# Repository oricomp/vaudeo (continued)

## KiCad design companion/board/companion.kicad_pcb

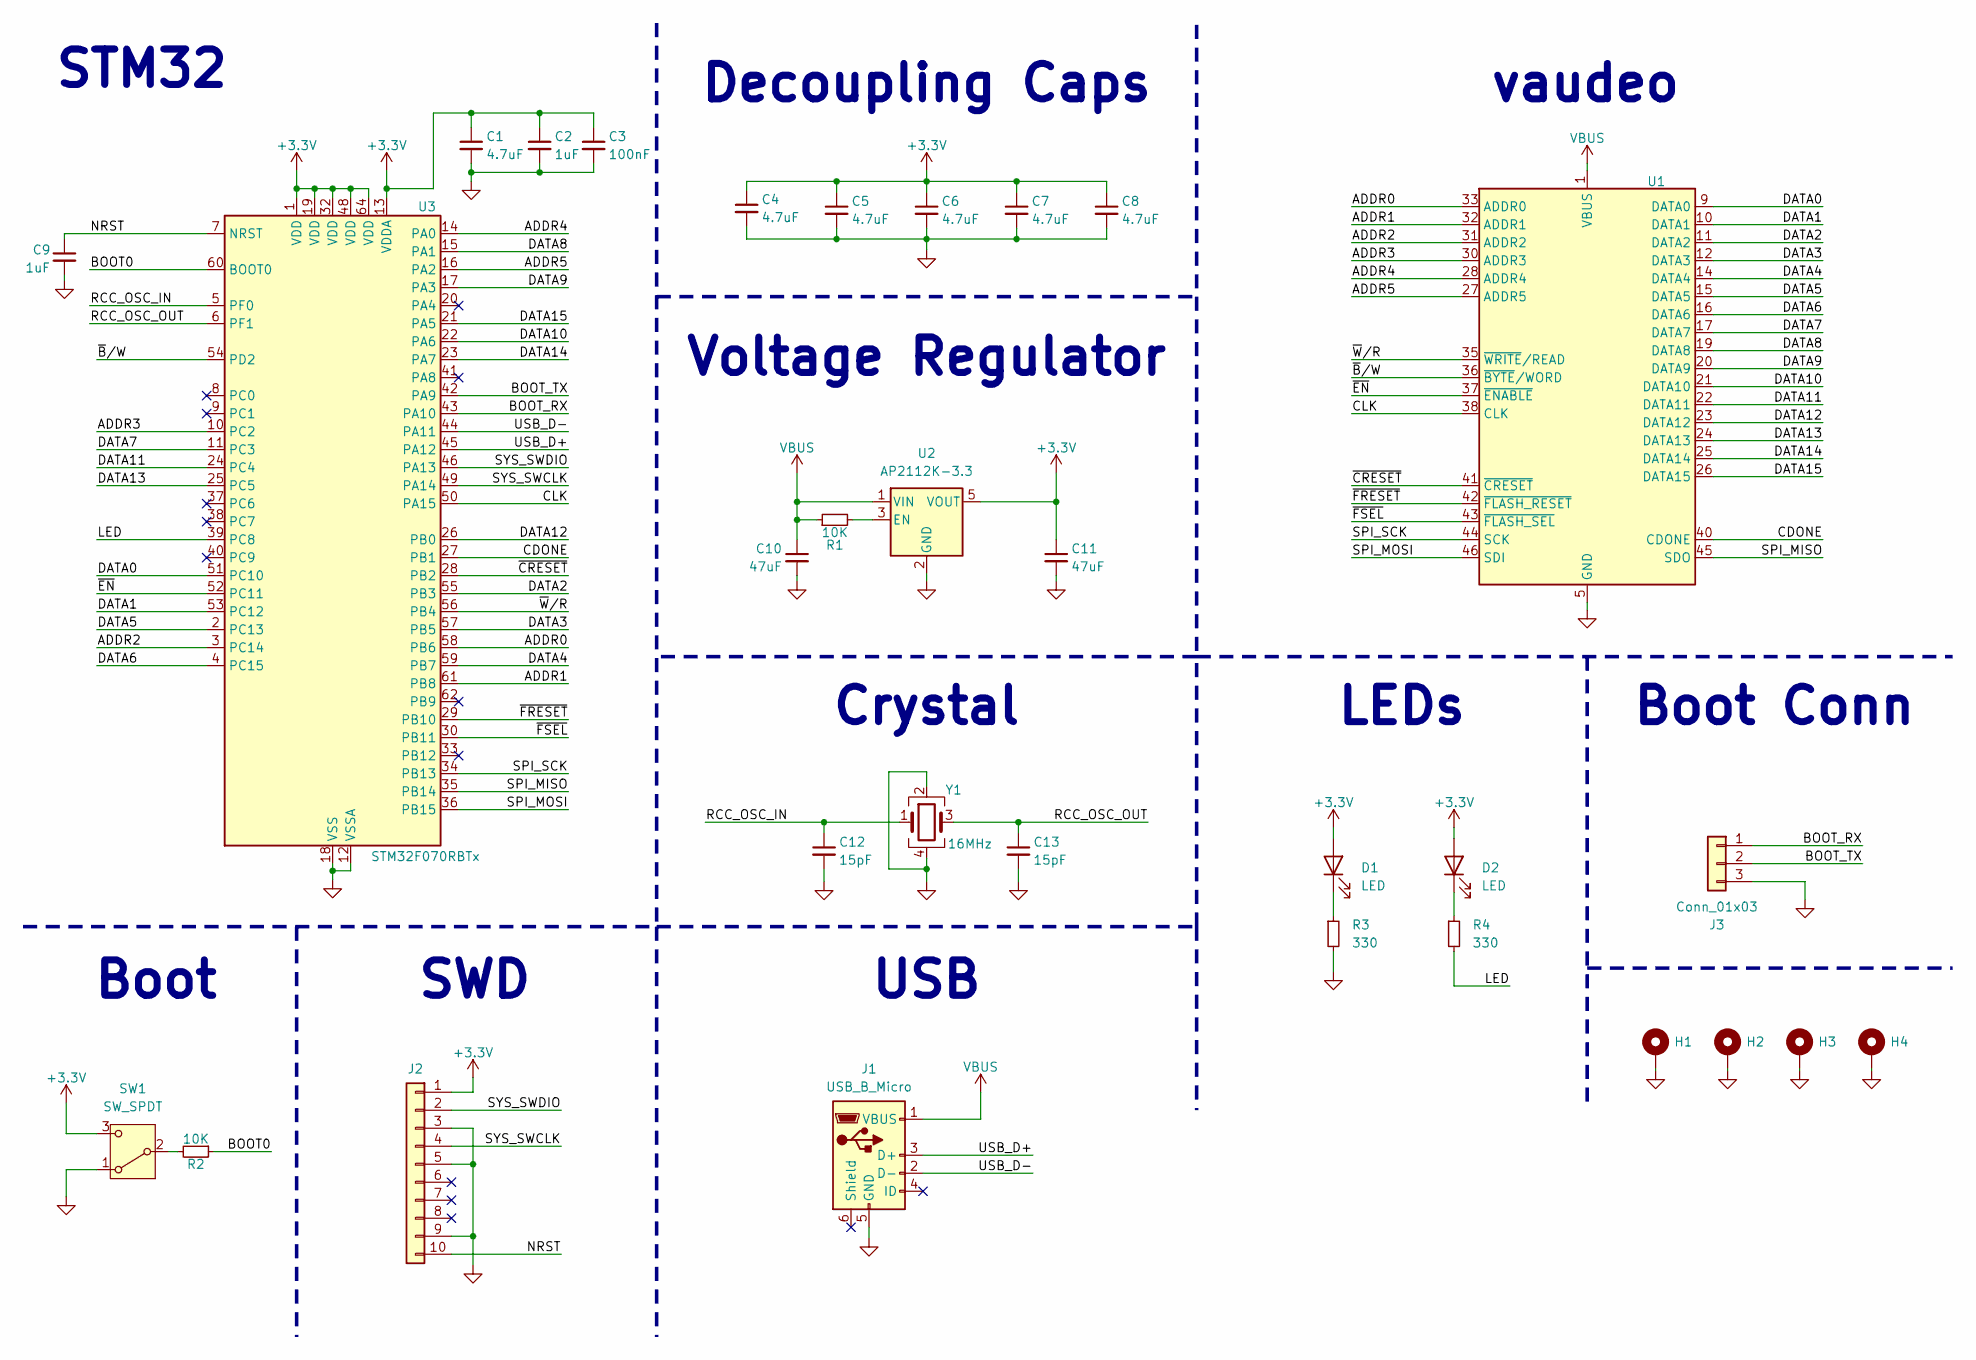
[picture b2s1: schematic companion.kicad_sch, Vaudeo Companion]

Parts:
C1, C4, C5, C6, C7, C8: 4.7uF; C_0805_2012Metric_Pad1.18x1.45mm_HandSolder
C2, C9: 1uF; C_0805_2012Metric_Pad1.18x1.45mm_HandSolder
C3: 100nF; C_0805_2012Metric_Pad1.18x1.45mm_HandSolder
C10, C11: 47uF; C_0805_2012Metric_Pad1.18x1.45mm_HandSolder
C12, C13: 15pF; C_0805_2012Metric_Pad1.18x1.45mm_HandSolder
D1, D2: LED; LED_0805_2012Metric_Pad1.15x1.40mm_HandSolder
H1, H2, H3, H4: MountingHole_Pad; MountingHole_3.2mm_M3_Pad_Via
J1: USB_B_Micro; USB_Micro-B_Amphenol_10118194_Horizontal
J2: Conn_01x10; PinHeader_1x10_P2.54mm_Horizontal
J3: Conn_01x03; PinHeader_1x03_P2.54mm_Horizontal
R1, R2: 10K; R_0805_2012Metric_Pad1.20x1.40mm_HandSolder
R3, R4: 330; R_0805_2012Metric_Pad1.20x1.40mm_HandSolder
SW1: SW_SPDT; SW_SPDT_CK_JS102011SAQN
U1: vaudeo
U2: AP2112K-3.3; SOT-23-5
U3: STM32F070RBTx; LQFP-64_10x10mm_P0.5mm
Y1: 16MHz; Crystal_SMD_SeikoEpson_TSX3225-4Pin_3.2x2.5mm_HandSoldering

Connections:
+3.3V: C1.1, C2.1, C3.1, C4.1, C5.1, C6.1, C7.1, C8.1, C11.1, D1.2 (A), D2.2 (A), J2.1, SW1.3 (C), U2.5 (VOUT), U3.1 (VDD), U3.13 (VDDA), U3.19 (VDD), U3.32 (VDD), U3.48 (VDD), U3.64 (VDD)
/ADDR0: U1.33 (ADDR0), U3.58 (PB6)
/ADDR1: U1.32 (ADDR1), U3.61 (PB8)
/ADDR2: U1.31 (ADDR2), U3.3 (PC14)
/ADDR3: U1.30 (ADDR3), U3.10 (PC2)
/ADDR4: U1.28 (ADDR4), U3.14 (PA0)
/ADDR5: U1.27 (ADDR5), U3.16 (PA2)
/BOOT0: R2.1, U3.60 (BOOT0)
/BOOT_RX: J3.1, U3.43 (PA10)
/BOOT_TX: J3.2, U3.42 (PA9)
/CDONE: U1.40 (CDONE), U3.27 (PB1)
/CLK: U1.38 (CLK), U3.50 (PA15)
/DATA0: U1.9 (DATA0), U3.51 (PC10)
/DATA1: U1.10 (DATA1), U3.53 (PC12)
/DATA2: U1.11 (DATA2), U3.55 (PB3)
/DATA3: U1.12 (DATA3), U3.57 (PB5)
/DATA4: U1.14 (DATA4), U3.59 (PB7)
/DATA5: U1.15 (DATA5), U3.2 (PC13)
/DATA6: U1.16 (DATA6), U3.4 (PC15)
/DATA7: U1.17 (DATA7), U3.11 (PC3)
/DATA8: U1.19 (DATA8), U3.15 (PA1)
/DATA9: U1.20 (DATA9), U3.17 (PA3)
/DATA10: U1.21 (DATA10), U3.22 (PA6)
/DATA11: U1.22 (DATA11), U3.24 (PC4)
/DATA12: U1.23 (DATA12), U3.26 (PB0)
/DATA13: U1.24 (DATA13), U3.25 (PC5)
/DATA14: U1.25 (DATA14), U3.23 (PA7)
/DATA15: U1.26 (DATA15), U3.21 (PA5)
/LED: R4.2, U3.39 (PC8)
/NRST: C9.1, J2.10, U3.7 (NRST)
/RCC_OSC_IN: C12.1, U3.5 (PF0), Y1.1
/RCC_OSC_OUT: C13.1, U3.6 (PF1), Y1.3
/SPI_MISO: U1.45 (SDO), U3.35 (PB14)
/SPI_MOSI: U1.46 (SDI), U3.36 (PB15)
/SPI_SCK: U1.44 (SCK), U3.34 (PB13)
/SYS_SWCLK: J2.4, U3.49 (PA14)
/SYS_SWDIO: J2.2, U3.46 (PA13)
/USB_D+: J1.3 (D+), U3.45 (PA12)
/USB_D-: J1.2 (D-), U3.44 (PA11)
/~B/W: U1.36 (~BYTE/WORD), U3.54 (PD2)
/~CRESET: U1.41 (~CRESET), U3.28 (PB2)
/~EN: U1.37 (~ENABLE), U3.52 (PC11)
/~FRESET: U1.42 (~FLASH_RESET), U3.29 (PB10)
/~FSEL: U1.43 (~FLASH_SEL), U3.30 (PB11)
/~W/R: U1.35 (~WRITE/READ), U3.56 (PB4)
GND: C1.2, C2.2, C3.2, C4.2, C5.2, C6.2, C7.2, C8.2, C9.2, C10.2, C11.2, C12.2, C13.2, H1.1, H2.1, H3.1, H4.1, J1.5 (GND), J2.3, J2.5, J2.9, J3.3, R3.2, SW1.1 (A), U1.5 (GND), U1.6 (GND), U1.7 (GND), U1.8 (GND), U1.13 (GND), U1.18 (GND), U1.29 (GND), U1.34 (GND), U1.39 (GND), U2.2 (GND), U3.12 (VSSA), U3.18 (VSS), U3.31 (VSS), U3.47 (VSS), U3.63 (VSS), Y1.2, Y1.4
unnamed: D1.1 (K), R3.1
unnamed: D2.1 (K), R4.1
unnamed: R2.2, SW1.2 (B)
unnamed: R1.2, U2.3 (EN)
VBUS: C10.1, J1.1 (VBUS), R1.1, U1.1 (VBUS), U1.2 (VBUS), U1.3 (VBUS), U1.4 (VBUS), U2.1 (VIN)

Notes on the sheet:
LEDs
Boot
SWD
Crystal
Boot Conn
Decoupling Caps
USB
STM32
vaudeo
Voltage Regulator

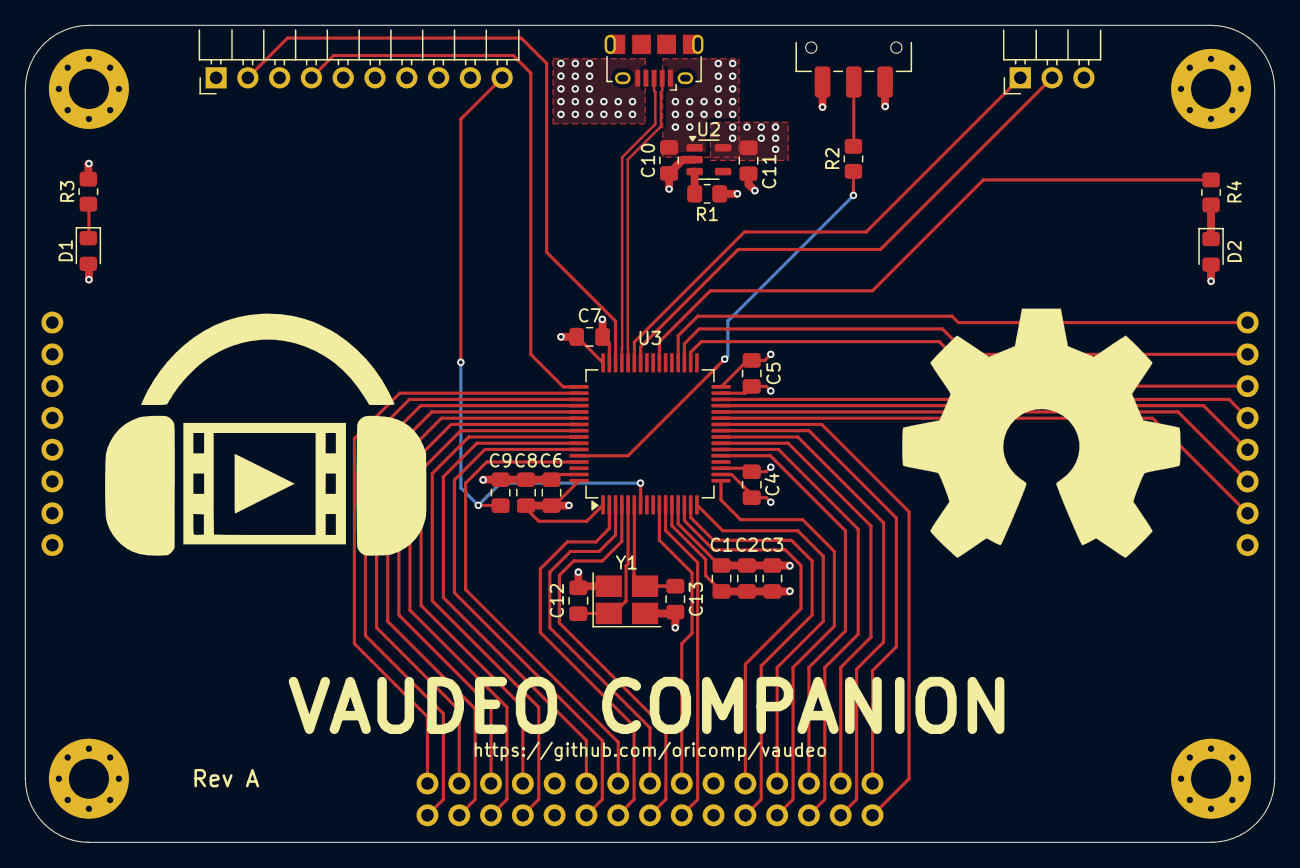
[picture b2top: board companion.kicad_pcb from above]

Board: 4 copper layers, 99.8 x 65.3 mm, 31 parts (0 on the bottom side), 51 nets.

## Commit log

2025-01-25 [META] Copy over files
2025-01-26 [Verilog][Test] basic counter with a test
    test uses cocotb
    current does not do anythin
2025-01-26 [Vaudeo][Counter] implement actual tests
